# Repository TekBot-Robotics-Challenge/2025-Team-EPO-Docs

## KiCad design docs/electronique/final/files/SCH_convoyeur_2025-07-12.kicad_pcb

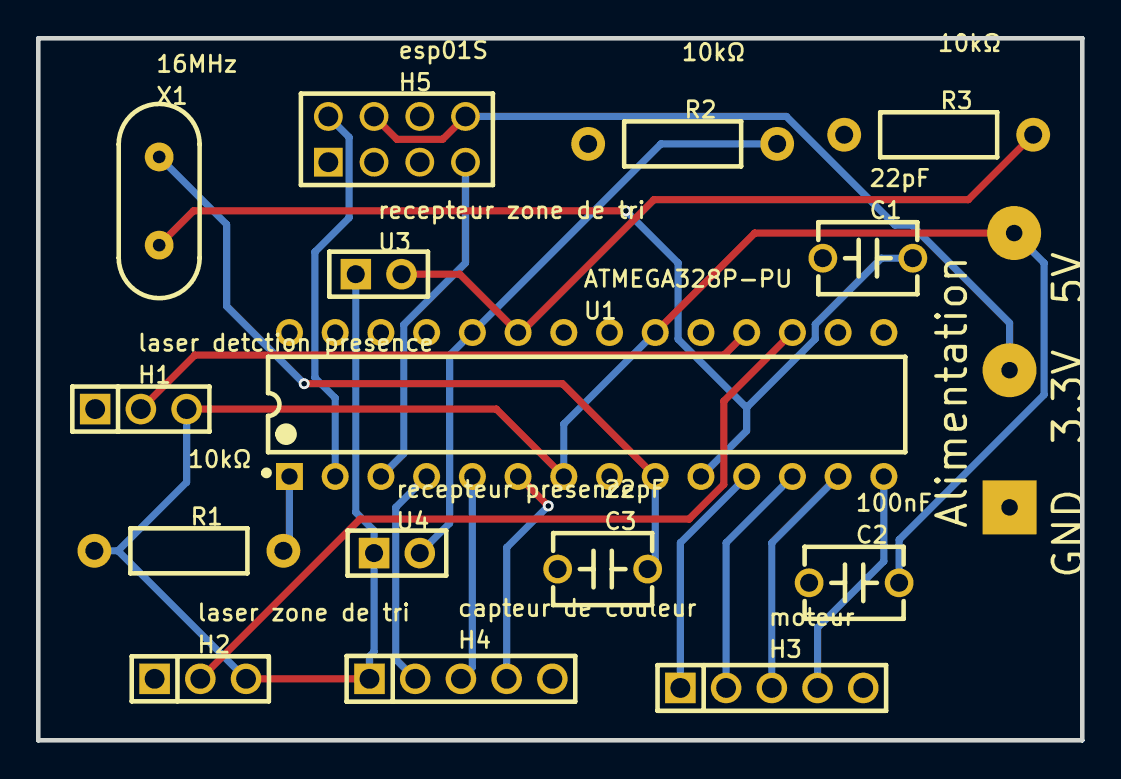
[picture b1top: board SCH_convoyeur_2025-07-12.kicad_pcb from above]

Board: 2 copper layers, 58.0 x 39.0 mm, 18 parts (0 on the bottom side), 19 nets.

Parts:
C1, C3: 22pF; CAP-TH_L5.5-W4.0-P5.00-D0.5
C2: 100nF; CAP-TH_L5.5-W4.0-P5.00-D0.5
H1: laser detction presence; HDR-TH_3P-P2.54-V-M
H2: laser zone de tri; HDR-TH_3P-P2.54-V-M
H3: moteur; HDR-TH_5P-P2.54-V-M
H4: capteur de couleur; HDR-TH_5P-P2.54-V-M
H5: esp01S; HDR-TH_8P-P2.54-V-F-R2-C4-S2.54
Pad_gge2154: Pad_gge2154
Pad_gge2184: Pad_gge2184
Pad_gge2229: Pad_gge2229
R1, R2, R3: 10kΩ; RES-TH_BD2.5-L6.5-P10.50-D0.6
U1: ATMEGA328P-PU; DIP-28_L34.6-W7.3-P2.54-LS10.2-BL
U3: recepteur zone de tri; HDR-TH_2P-P2.54-V-F
U4: recepteur presence; HDR-TH_2P-P2.54-V-F
X1: 16MHz; OSC-TH_L10.0-W4.5-P5.00

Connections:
11: H2.2, U1.17
12: H1.2, U1.18
+3.3V: H5.4, H5.8, Pad_gge2229.1
+5V: C2.2, H1.3, H2.3, H4.1, Pad_gge2154.1, R1.1, U1.7, U1.20, U3.1, U4.1
A0: R3.2, U1.23, U3.2
A1: R2.2, U1.24, U4.2
GND: C1.1, C2.1, C3.1, H1.1, H2.1, H3.5, H4.5, H5.1, Pad_gge2184.2, R2.1, R3.1, U1.8, U1.22
H3_1: H3.1, U1.11
H3_2: H3.2, U1.12
H3_3: H3.3, U1.13
H3_4: H3.4, U1.14
H4_2: H4.2, U1.4
H4_3: H4.3, U1.5
H4_4: H4.4, U1.6
RX_ATMEGA: H5.2, U1.2
TX_ATMEGA: H5.7, U1.3
U1_1: R1.2, U1.1
U1_9: C3.2, U1.9, X1.1
U1_10: C1.2, U1.10, X1.2

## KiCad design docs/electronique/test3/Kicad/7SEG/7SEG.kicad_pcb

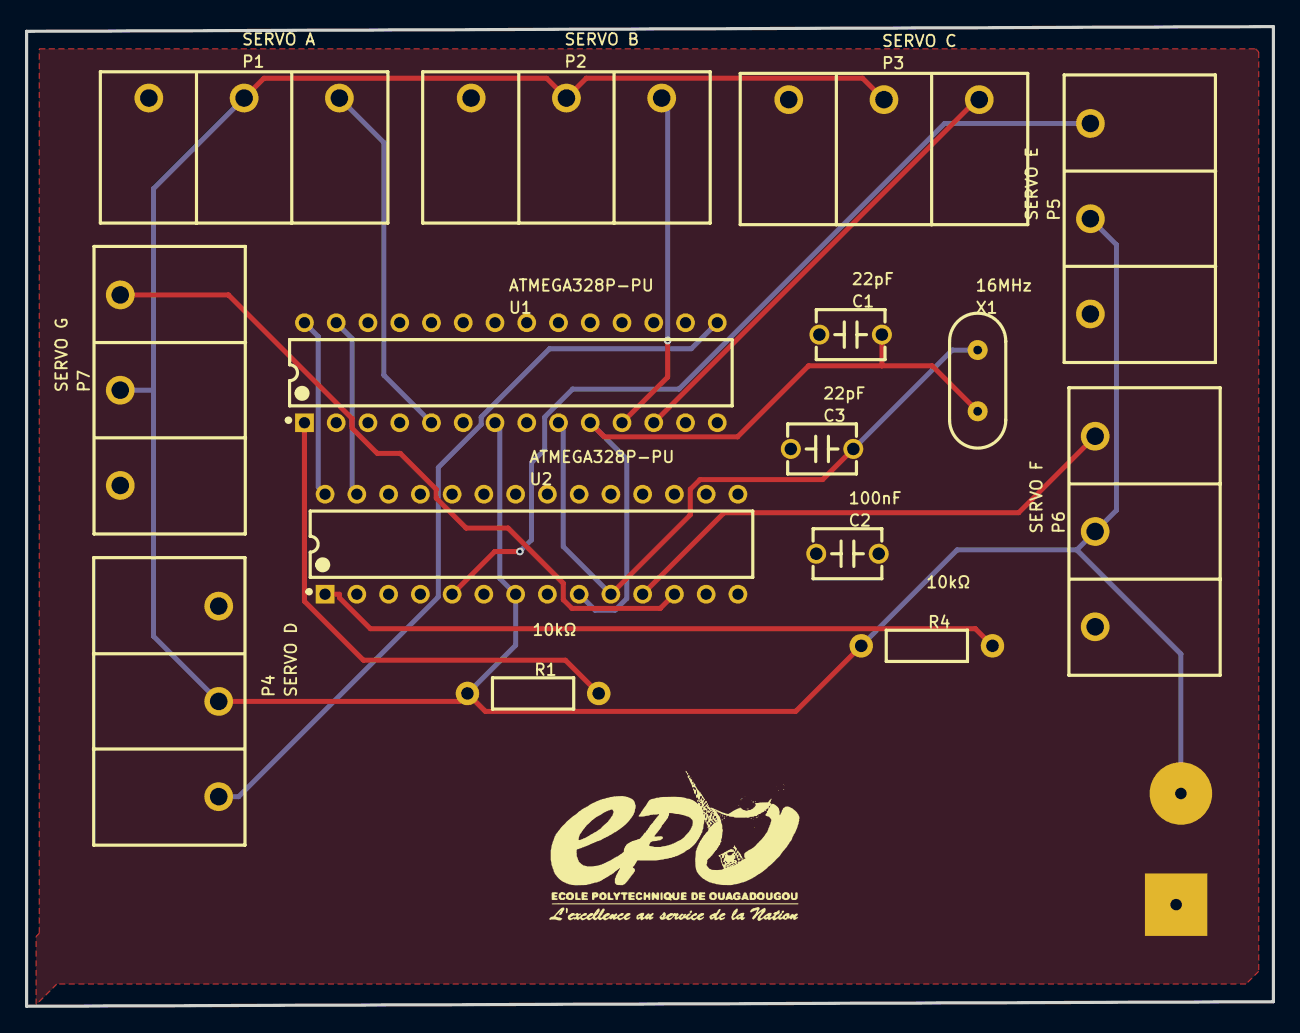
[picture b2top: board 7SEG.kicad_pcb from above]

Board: 2 copper layers, 99.7 x 78.4 mm, 17 parts (0 on the bottom side), 15 nets.

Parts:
C1, C3: 22pF; CAP-TH_L5.5-W4.0-P5.00-D0.5
C2: 100nF; CAP-TH_L5.5-W4.0-P5.00-D0.5
P1: SERVO A; CONN-TH_3P-P7.62_HEADER3
P2: SERVO B; CONN-TH_3P-P7.62_HEADER3
P3: SERVO C; CONN-TH_3P-P7.62_HEADER3
P4: SERVO D; CONN-TH_3P-P7.62_HEADER3
P5: SERVO E; CONN-TH_3P-P7.62_HEADER3
P6: SERVO F; CONN-TH_3P-P7.62_HEADER3
P7: SERVO G; CONN-TH_3P-P7.62_HEADER3
Pad_gge2604: Pad_gge2604
Pad_gge2622: Pad_gge2622
R1, R4: 10kΩ; RES-TH_BD2.5-L6.5-P10.50-D0.6
U1, U2: ATMEGA328P-PU; DIP-28_L34.6-W7.3-P2.54-LS10.2-BL
X1: 16MHz; OSC-TH_L10.0-W4.5-P5.00

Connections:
+5V: P1.2, P2.2, P3.2, P4.2, P5.2, P6.2, P7.2, Pad_gge2604.1, R1.1, R4.1, U1.7, U2.7
GND: C1.1, C2.1, C3.1, P1.1, P2.1, P3.1, P4.1, P5.1, P6.1, P7.1, Pad_gge2622.2, U1.8, U1.22, U2.8, U2.22
SERVO_A: P1.3, U1.5
SERVO_B: P2.3, U1.11
SERVO_C: P3.3, U1.12
SERVO_D: P4.3, U1.15
SERVO_E: P5.3, U2.5
SERVO_F: P6.3, U2.11
SERVO_G: P7.3, U2.12
U1_1: R1.2, U1.1
U1_9: C3.2, U1.9, U2.10, X1.1
U1_10: C1.2, U1.10, U2.9, X1.2
U1_27: U1.27, U2.27
U1_28: U1.28, U2.28
U2_1: R4.2, U2.1

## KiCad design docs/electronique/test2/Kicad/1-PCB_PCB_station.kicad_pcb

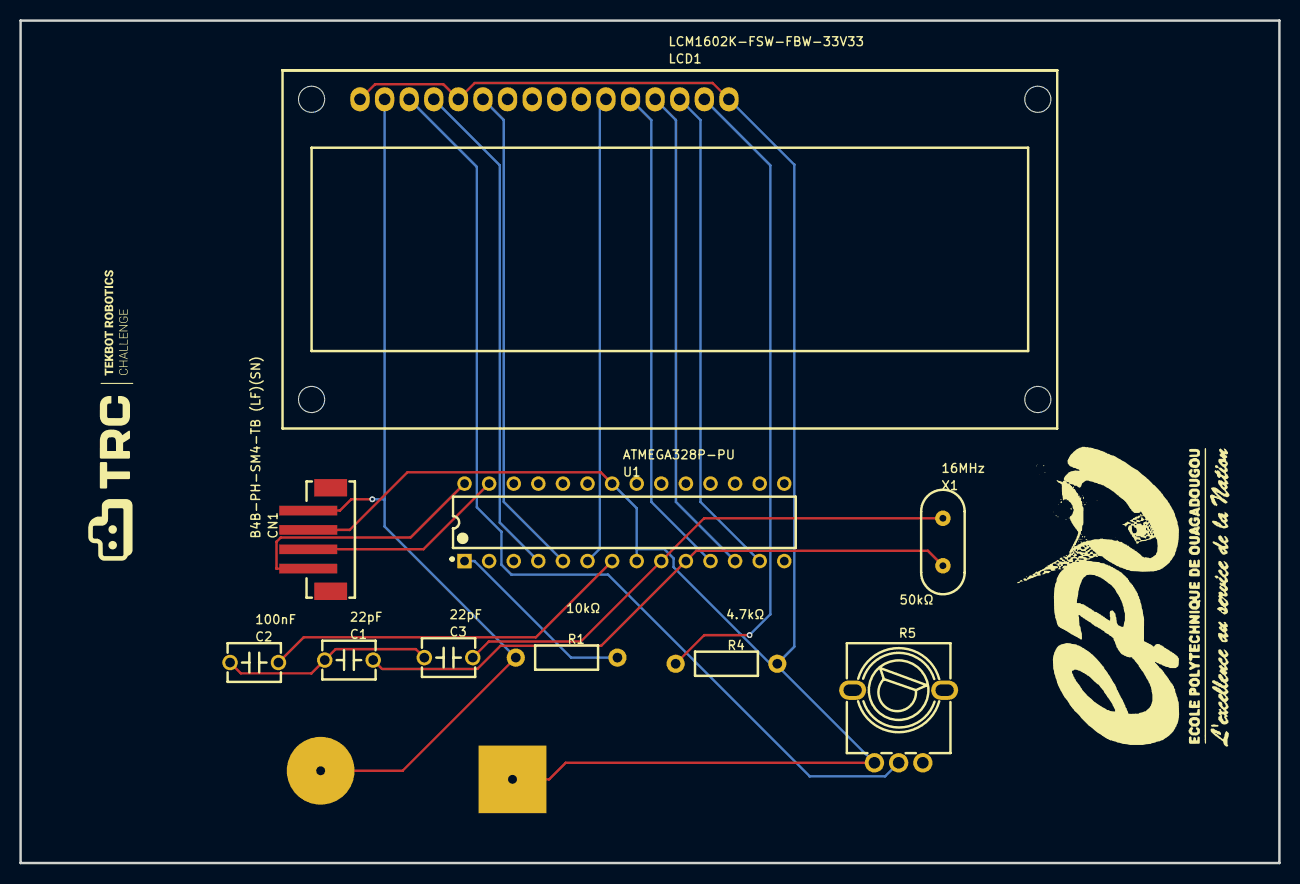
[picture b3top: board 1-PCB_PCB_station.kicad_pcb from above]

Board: 2 copper layers, 130.0 x 87.0 mm, 12 parts (0 on the bottom side), 17 nets.

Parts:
C1, C3: 22pF; CAP-TH_L5.5-W4.0-P5.00-D0.5
C2: 100nF; CAP-TH_L5.5-W4.0-P5.00-D0.5
CN1: B4B-PH-SM4-TB (LF)(SN); CONN-SMD_B4B-PH-SM4-TB-LF-SN
LCD1: LCM1602K-FSW-FBW-33V33; MODULE-TH_LCM1602K
Pad_gge2175: Pad_gge2175
Pad_gge2211: Pad_gge2211
R1: 10kΩ; RES-TH_BD2.5-L6.5-P10.50-D0.6
R4: 4.7kΩ; RES-TH_BD2.5-L6.5-P10.50-D0.6
R5: 50kΩ; RES-ADJ-TH_RK09L1140A5P
U1: ATMEGA328P-PU; DIP-28_L34.6-W7.3-P2.54-LS10.2-BL
X1: 16MHz; OSC-TH_L10.0-W4.5-P5.00

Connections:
+5V: CN1.1, LCD1.2, Pad_gge2175.1, R1.1
C1_2: C1.2, U1.10, X1.2
C2_2: C2.2, U1.7
C3_1: C1.1, C2.1, C3.1
C3_2: C3.2, U1.9, X1.1
CN1_3: CN1.3, U1.27
CN1_4: CN1.4, U1.28
GND: CN1.2, LCD1.1, LCD1.5, LCD1.16, Pad_gge2211.1, R4.2, R5.1, U1.8, U1.22
LCD1_3: LCD1.3, R5.2
LCD1_15: LCD1.15, R4.1
R1_2: R1.2, U1.1
U1_4: LCD1.4, U1.4
U1_5: LCD1.6, U1.5
U1_6: LCD1.11, U1.6
U1_11: LCD1.12, U1.11
U1_12: LCD1.13, U1.12
U1_13: LCD1.14, U1.13

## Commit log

2025-06-12 Add build files
2025-06-12 maj du site
2025-06-12 maj site
2025-06-16 commit du 16 juin
2025-06-17 ajout du dossier docs
2025-06-17 maj du test 2
2025-06-17 maj du site avec ajout des pieces du test 1
2025-06-19 ajout des images meca
2025-06-19 ajout des images de l'assemblage test 2
2025-06-19 add images
2025-06-19 push week 2
2025-06-21 test 2 edit
2025-06-22 maj du 22 jun
2025-06-23 23 juin
2025-06-25 images electronique
2025-06-26 26 jun
2025-06-26 maj de la doc avec electro et info
2025-06-26 maj de la doc meca
2025-07-10 maj du 10 juillet
2025-07-12 juillet 12
2025-07-12 add alimentation
2025-07-26 maj du 26 juil
